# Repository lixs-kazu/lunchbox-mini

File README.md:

# lunchbox-mini

40(48)キーの小型キーボード

トッププレートにもpro microのフットプリントを配置することによってchocスイッチが使用可能

ble micro proを使用した際に簡単にBLE接続先に接続できるようにタクトスイッチをキーボード側面に配置

通常のpro microも使用できるようにTRRSコネクタを配置（I2Cには対応してません）

キーピッチは縦・横ともに19mmなのでキーキャップを削る必要はありません

# ビルドガイド

スイッチをつける前にTRRSコネクタとRESET用のタクトスイッチをつける以外は他のキーボードと同じです。

ファームはありません。（一応helixと同じpin配置にしてあるのでhelixのファームが使用できます。）

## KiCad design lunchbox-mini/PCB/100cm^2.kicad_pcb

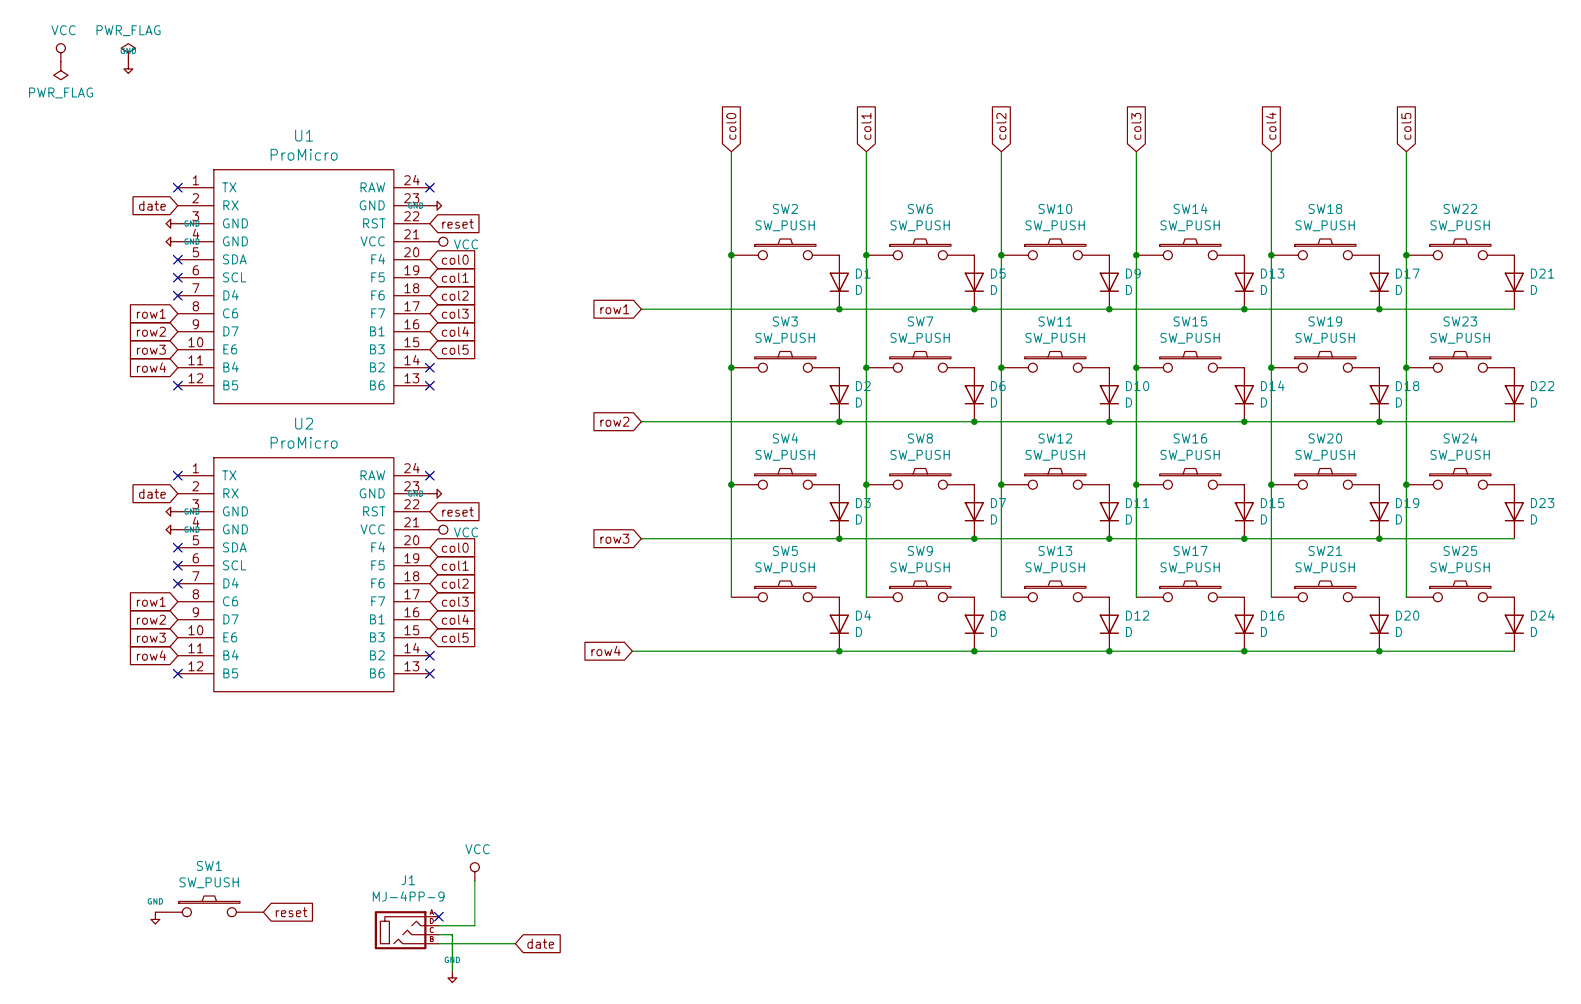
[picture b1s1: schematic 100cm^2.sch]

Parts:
D1, D2, D3, D4, D5, D6, D7, D8, D9, D10, D11, D12, D13, D14, D15, D16, D17, D18, D19, D20, D21, D22, D23, D24: D; D3_SMD
J1: MJ-4PP-9
SW1, SW22, SW23, SW24, SW25: SW_PUSH; ResetSW
SW2, SW3, SW4, SW5, SW6, SW7, SW8, SW9, SW10, SW11, SW12, SW13, SW14, SW15, SW16, SW17, SW18, SW19, SW20, SW21: SW_PUSH; MX_PG1350_FLIP_HOLES
U1, U2: ProMicro; ProMicro_v2_1side

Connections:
+5V: J1.C, SW1.1, U1.3 (GND), U1.4 (GND), U1.23 (GND), U2.3 (GND), U2.4 (GND), U2.23 (GND)
unnamed: D1.2 (A), SW2.2
unnamed: D2.2 (A), SW3.2
unnamed: D3.2 (A), SW4.2
unnamed: D4.2 (A), SW5.2
unnamed: D5.2 (A), SW6.2
unnamed: D6.2 (A), SW7.2
unnamed: D7.2 (A), SW8.2
unnamed: D8.2 (A), SW9.2
unnamed: D9.2 (A), SW10.2
unnamed: D10.2 (A), SW11.2
unnamed: D11.2 (A), SW12.2
unnamed: D12.2 (A), SW13.2
unnamed: D13.2 (A), SW14.2
unnamed: D14.2 (A), SW15.2
unnamed: D15.2 (A), SW16.2
unnamed: D16.2 (A), SW17.2
unnamed: D17.2 (A), SW18.2
unnamed: D18.2 (A), SW19.2
unnamed: D19.2 (A), SW20.2
unnamed: D20.2 (A), SW21.2
unnamed: D21.2 (A), SW22.2
unnamed: D22.2 (A), SW23.2
unnamed: D23.2 (A), SW24.2
unnamed: D24.2 (A), SW25.2
VCC: J1.D, U1.21 (VCC), U2.21 (VCC)
col0: SW2.1, SW3.1, SW4.1, SW5.1, U1.20 (F4), U2.20 (F4)
col1: SW6.1, SW7.1, SW8.1, SW9.1, U1.19 (F5), U2.19 (F5)
col2: SW10.1, SW11.1, SW12.1, SW13.1, U1.18 (F6), U2.18 (F6)
col3: SW14.1, SW15.1, SW16.1, SW17.1, U1.17 (F7), U2.17 (F7)
col4: SW18.1, SW19.1, SW20.1, SW21.1, U1.16 (B1), U2.16 (B1)
col5: SW22.1, SW23.1, SW24.1, SW25.1, U1.15 (B3), U2.15 (B3)
date: J1.B, U1.2 (RX), U2.2 (RX)
reset: SW1.2, U1.22 (RST), U2.22 (RST)
row1: D1.1 (K), D5.1 (K), D9.1 (K), D13.1 (K), D17.1 (K), D21.1 (K), U1.8 (C6), U2.8 (C6)
row2: D2.1 (K), D6.1 (K), D10.1 (K), D14.1 (K), D18.1 (K), D22.1 (K), U1.9 (D7), U2.9 (D7)
row3: D3.1 (K), D7.1 (K), D11.1 (K), D15.1 (K), D19.1 (K), D23.1 (K), U1.10 (E6), U2.10 (E6)
row4: D4.1 (K), D8.1 (K), D12.1 (K), D16.1 (K), D20.1 (K), D24.1 (K), U1.11 (B4), U2.11 (B4)

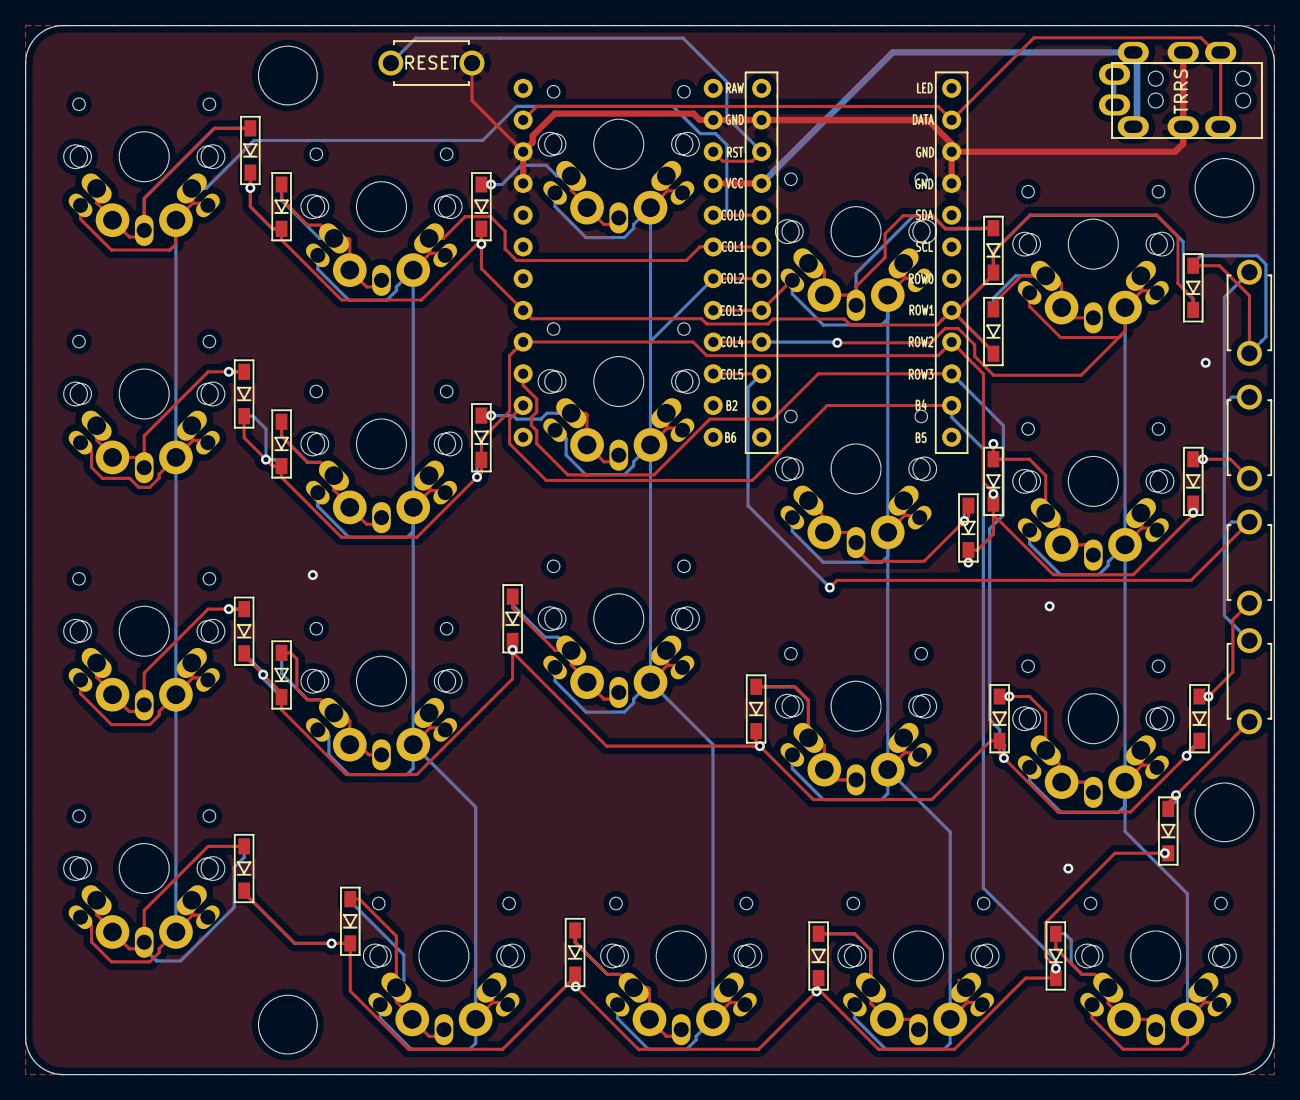
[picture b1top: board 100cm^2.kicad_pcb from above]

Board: 2 copper layers, 100.0 x 84.0 mm, 56 parts (1 on the bottom side), 38 nets.

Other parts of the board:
HOLE_3M, HOLE_3M#2, HOLE_3M#3, HOLE_3M#4: VAL**; HOLE_M2_TH
